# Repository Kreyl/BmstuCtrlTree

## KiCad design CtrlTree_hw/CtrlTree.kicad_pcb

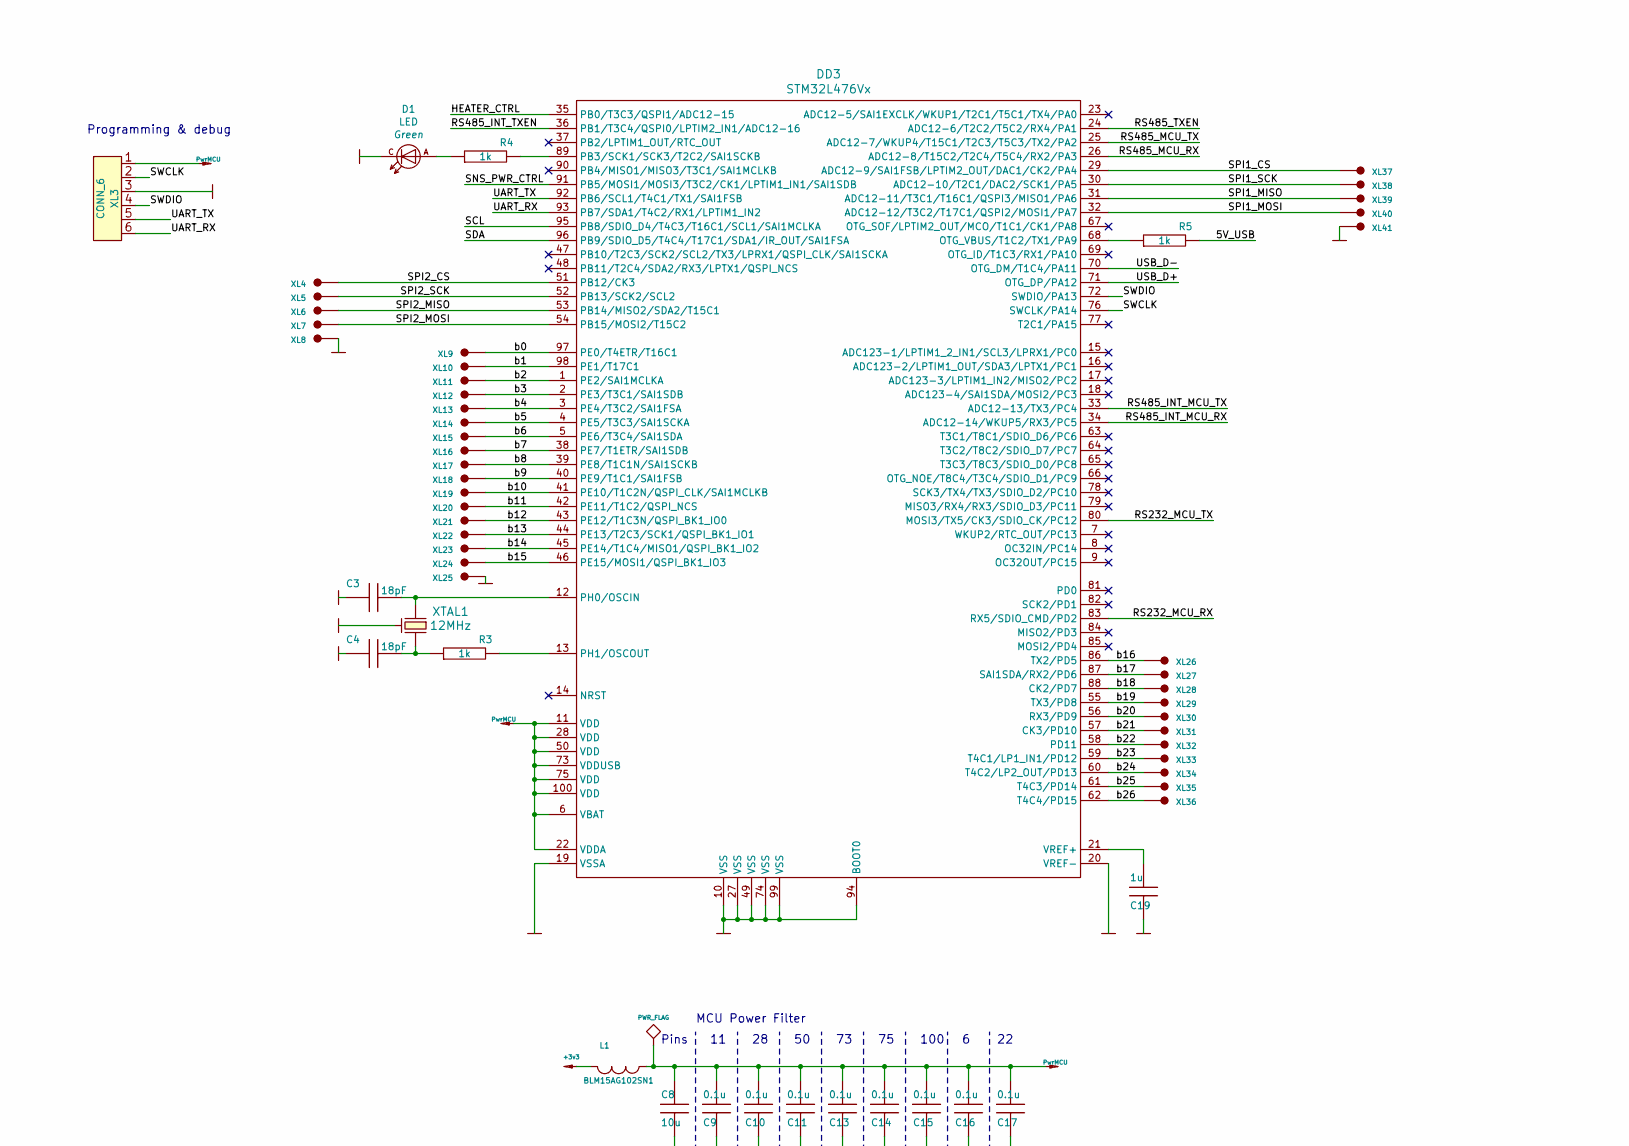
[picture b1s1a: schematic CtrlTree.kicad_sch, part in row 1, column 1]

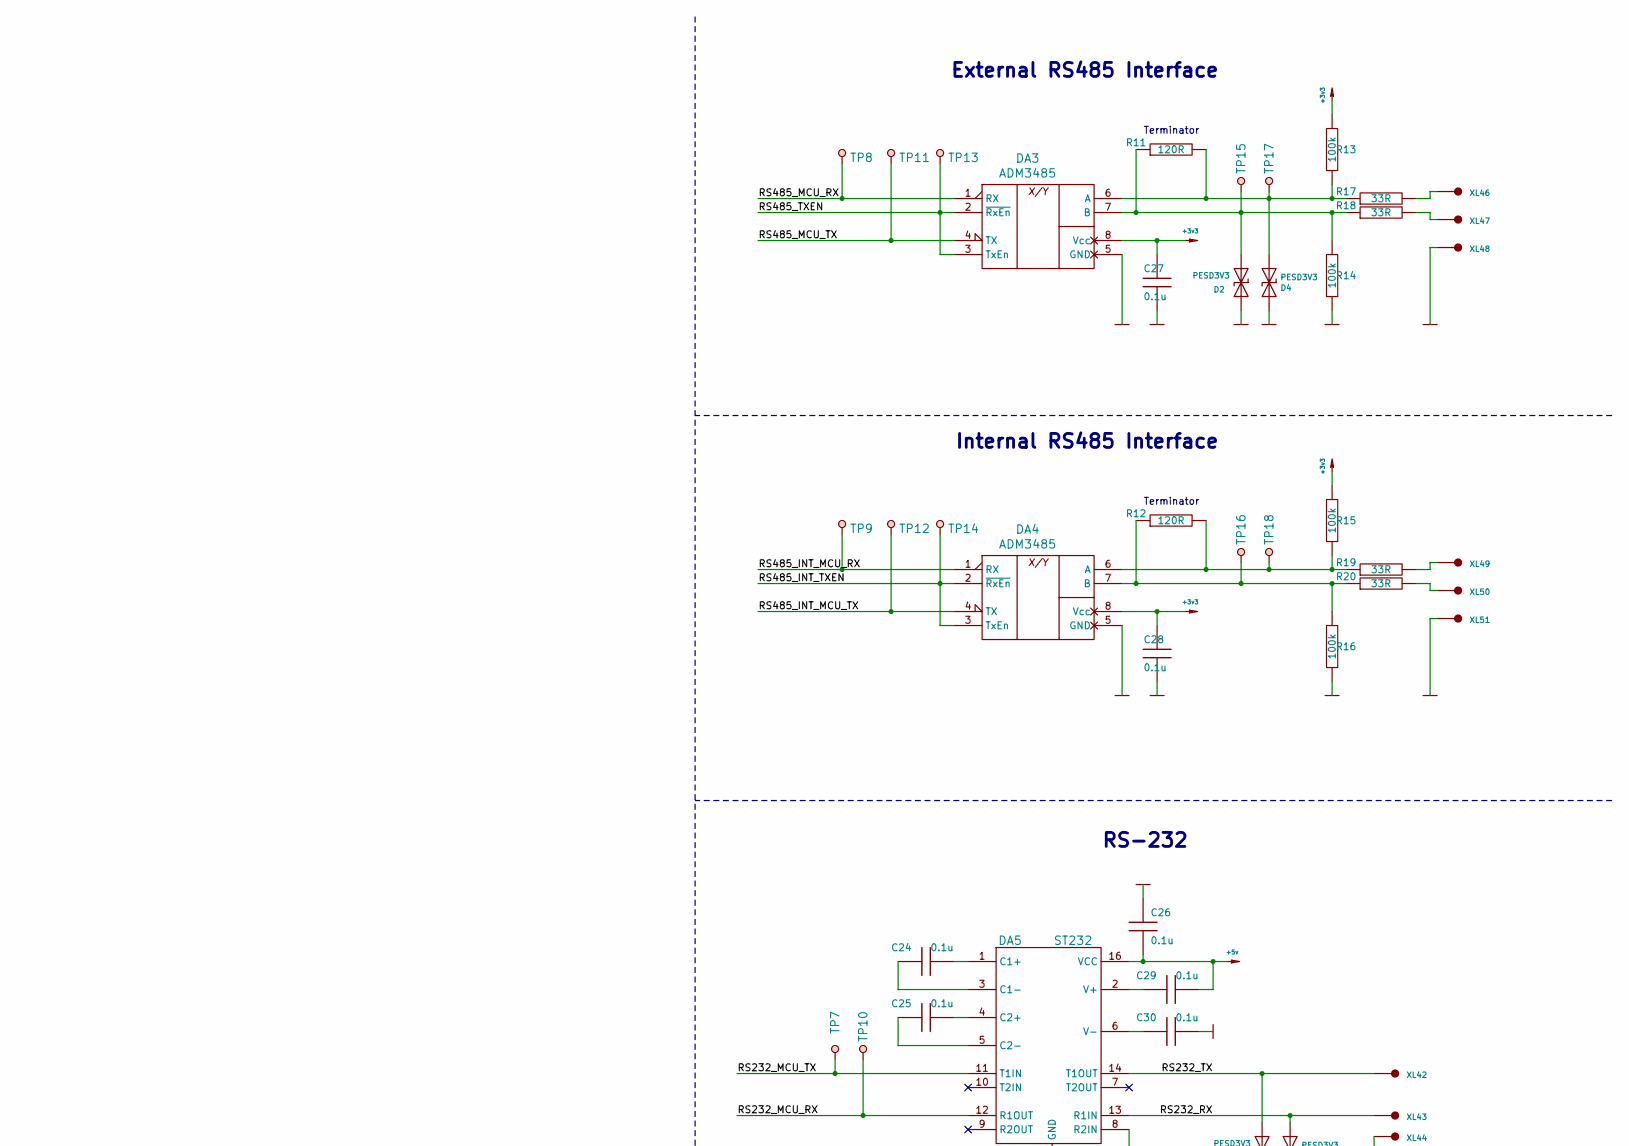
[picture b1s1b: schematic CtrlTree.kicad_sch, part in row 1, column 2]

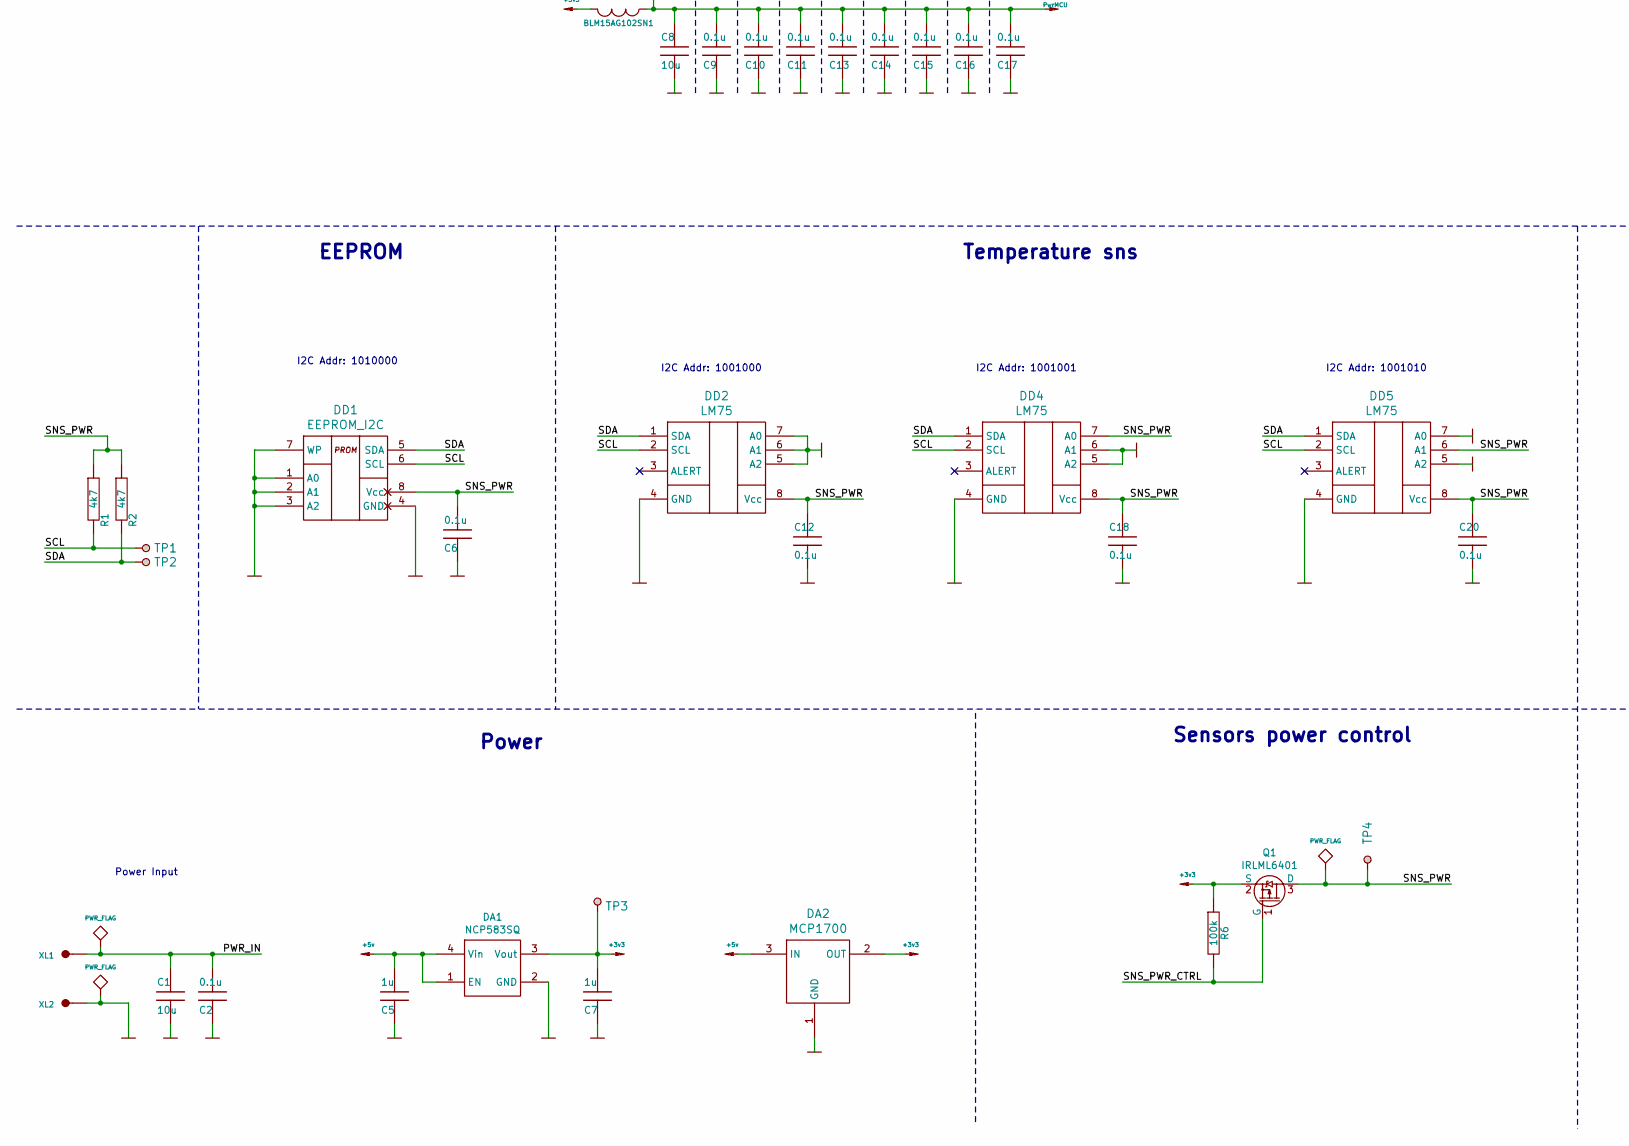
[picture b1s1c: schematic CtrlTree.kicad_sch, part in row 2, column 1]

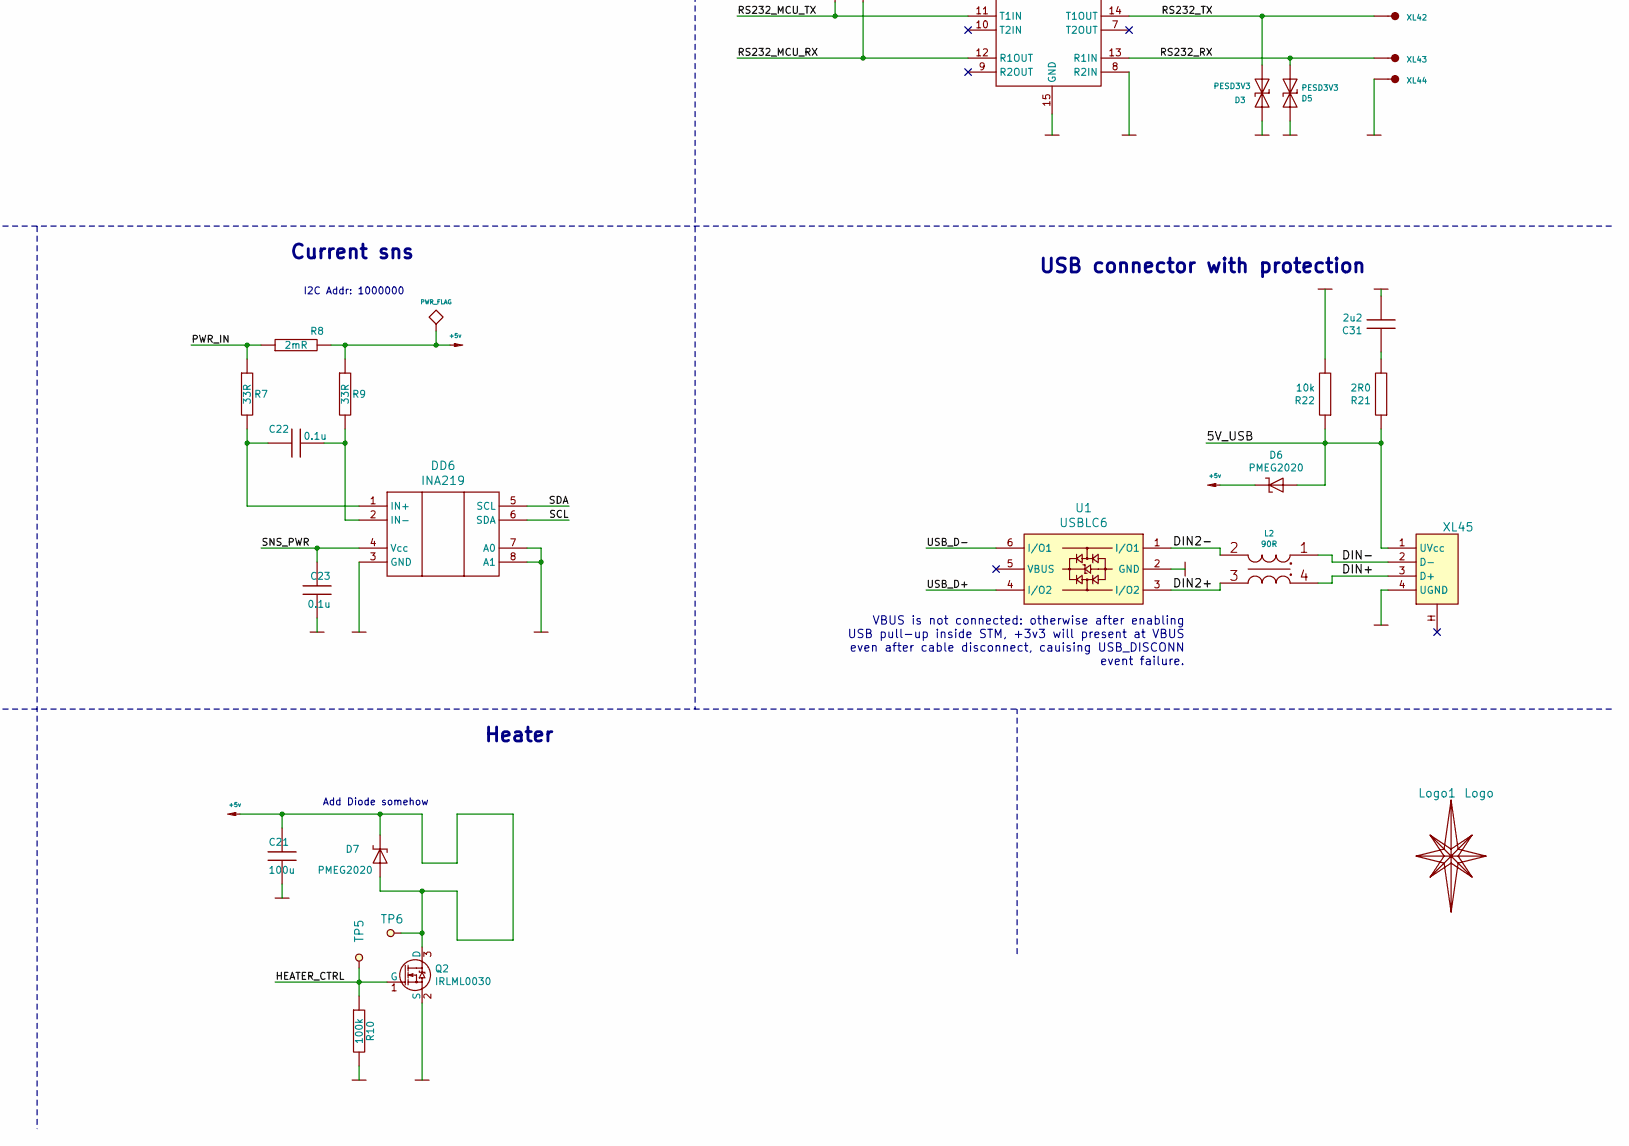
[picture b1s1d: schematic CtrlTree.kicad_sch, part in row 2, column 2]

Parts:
C1, C8: 10u; CAP_0603_Silks
C2, C6, C9, C10, C11, C12, C13, C14, C15, C16, C17, C18, C20, C22, C23, C24, C25, C26, C27, C28, C29, C30: 0.1u; CAP_0603_Silks
C3, C4: 18pF; CAP_0603_Silks
C5, C7, C19: 1u; CAP_0603_Silks
C21: 100u; CAP_1206
C31: 2u2; CAP_0603_Silks
D1: LED; LED_0603
D2, D3, D4, D5: PESD3V3; SOD323
D6, D7: PMEG2020; SOD323
DA1: NCP583SQ; SC82AB
DA2: MCP1700; SOT23-3A
DA3, DA4: ADM3485; SO8_150MIL
DA5: ST232; SO16_150MIL
DD1: EEPROM_I2C; SO8_150MIL
DD2, DD4, DD5: LM75; SO8_150MIL
DD3: STM32L476Vx; LQFP100
DD6: INA219; SOT23-8
L1: BLM15AG102SN1; IND_0402
L2: 90R; DLW21SN
Logo1: Logo; Ostranna_12d7_10d1
Q1: IRLML6401; SOT23-3
Q2: IRLML0030; SOT23-3
R1, R2: 4k7; RES_0603
R3, R4, R5: 1k; RES_0603
R6, R10, R13, R14, R15, R16: 100k; RES_0603
R7, R9, R17, R18, R19, R20: 33R; RES_0603
R8: 2mR; RES_2512
R11, R12: 120R; RES_0603
R21: 2R0; RES_0603
R22: 10k; RES_0603
TP1, TP2, TP3, TP4, TP5, TP6, TP7, TP8, TP9, TP10, TP11, TP12, TP13, TP14, TP15, TP16, TP17, TP18: TESTPOINT; TESTPOINT_1MM
U1: USBLC6; SOT23-6
XL1, XL2, XL4, XL5, XL6, XL7, XL8, XL9, XL10, XL11, XL12, XL13, XL14, XL15, XL16, XL17, XL18, XL19, XL20, XL21, XL22, XL23, XL24, XL25, XL26, XL27, XL28, XL29, XL30, XL31, XL32, XL33, XL34, XL35, XL36, XL37, XL38, XL39, XL40, XL41, XL42, XL43, XL44, XL46, XL47, XL48, XL49, XL50, XL51: CONN_GOST_1; Oval3x1.5
XL3: CONN_6; PLS-6_LOCK
XL45: USB_MICRO_2H; USB_B
XTAL1: 12MHz; 03225C4

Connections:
+3v3: C7.1, C27.2, C28.2, DA1.3 (Vout), DA2.2 (OUT), DA3.8 (Vcc), DA4.8 (Vcc), L1.2, Q1.2 (S), R6.1, R13.1, R15.1, TP3.1
+5v: C5.1, C21.2, C26.2, C29.2, D6.C, D7.A, D7.C, DA1.1 (EN), DA1.4 (Vin), DA2.3 (IN), DA5.16 (VCC), Q2.3 (D), R8.2, R9.1, TP6.1
/5V_USB: D6.A, R5.2, R21.1, R22.1, XL45.1 (UVcc)
/DIN2+: L2.3, U1.3 (I/O2)
/DIN2-: L2.2, U1.1 (I/O1)
/DIN+: L2.4, XL45.3 (D+)
/DIN-: L2.1, XL45.2 (D-)
/HEATER_CTRL: DD3.35 (PB0/T3C3/QSPI1/ADC12-15), Q2.1 (G), R10.1, TP5.1
/PWR_IN: C1.2, C2.1, R7.1, R8.1, XL1.1
/RS232_MCU_RX: DA5.12 (R1OUT), DD3.83 (RX5/SDIO_CMD/PD2), TP10.1
/RS232_MCU_TX: DA5.11 (T1IN), DD3.80 (MOSI3/TX5/CK3/SDIO_CK/PC12), TP7.1
/RS232_RX: D5.C, DA5.13 (R1IN), XL43.1
/RS232_TX: D3.C, DA5.14 (T1OUT), XL42.1
/RS485_INT_MCU_RX: DA4.1 (RX), DD3.34 (ADC12-14/WKUP5/RX3/PC5), TP9.1
/RS485_INT_MCU_TX: DA4.4 (TX), DD3.33 (ADC12-13/TX3/PC4), TP12.1
/RS485_INT_TXEN: DA4.2 (~RxEn), DA4.3 (TxEn), DD3.36 (PB1/T3C4/QSPI0/LPTIM2_IN1/ADC12-16), TP14.1
/RS485_MCU_RX: DA3.1 (RX), DD3.26 (ADC12-8/T15C2/T2C4/T5C4/RX2/PA3), TP8.1
/RS485_MCU_TX: DA3.4 (TX), DD3.25 (ADC12-7/WKUP4/T15C1/T2C3/T5C3/TX2/PA2), TP11.1
/RS485_TXEN: DA3.2 (~RxEn), DA3.3 (TxEn), DD3.24 (ADC12-6/T2C2/T5C2/RX4/PA1), TP13.1
/SCL: DD1.6 (SCL), DD2.2 (SCL), DD3.95 (PB8/SDIO_D4/T4C3/T16C1/SCL1/SAI1MCLKA), DD4.2 (SCL), DD5.2 (SCL), DD6.6 (SDA), R1.2, TP1.1
/SDA: DD1.5 (SDA), DD2.1 (SDA), DD3.96 (PB9/SDIO_D5/T4C4/T17C1/SDA1/IR_OUT/SAI1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), DD4.1 (SDA), DD5.1 (SDA), DD6.5 (SCL), R2.2, TP2.1
/SNS_PWR: C6.1, C12.2, C18.2, C20.2, C23.2, DD1.8 (Vcc), DD2.8 (Vcc), DD4.7 (A0), DD4.8 (Vcc), DD5.6 (A1), DD5.8 (Vcc), DD6.4 (Vcc), Q1.3 (D), R1.1, R2.1, TP4.1
/SNS_PWR_CTRL: DD3.91 (PB5/MOSI1/MOSI3/T3C2/CK1/LPTIM1_IN1/SAI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), Q1.1 (G), R6.2
/SPI1_CS: DD3.29 (ADC12-9/SAI1FSB/LPTIM2_OUT/DAC1/CK2/PA4), XL37.1
/SPI1_MISO: DD3.31 (ADC12-11/T3C1/T16C1/QSPI3/MISO1/PA6), XL39.1
/SPI1_MOSI: DD3.32 (ADC12-12/T3C2/T17C1/QSPI2/MOSI1/PA7), XL40.1
/SPI1_SCK: DD3.30 (ADC12-10/T2C1/DAC2/SCK1/PA5), XL38.1
/SPI2_CS: DD3.51 (PB12/CK3), XL4.1
/SPI2_MISO: DD3.53 (PB14/MISO2/SDA2/T15C1), XL6.1
/SPI2_MOSI: DD3.54 (PB15/MOSI2/T15C2), XL7.1
/SPI2_SCK: DD3.52 (PB13/SCK2/SCL2), XL5.1
/SWCLK: DD3.76 (SWCLK/PA14), XL3.2
/SWDIO: DD3.72 (SWDIO/PA13), XL3.4
/UART_RX: DD3.93 (PB7/SDA1/T4C2/RX1/LPTIM1_IN2), XL3.6
/UART_TX: DD3.92 (PB6/SCL1/T4C1/TX1/SAI1FSB), XL3.5
/USB_D+: DD3.71 (OTG_DP/PA12), U1.4 (I/O2)
/USB_D-: DD3.70 (OTG_DM/T1C4/PA11), U1.6 (I/O1)
/b0: DD3.97 (PE0/T4ETR/T16C1), XL9.1
/b1: DD3.98 (PE1/T17C1), XL10.1
/b2: DD3.1 (PE2/SAI1MCLKA), XL11.1
/b3: DD3.2 (PE3/T3C1/SAI1SDB), XL12.1
/b4: DD3.3 (PE4/T3C2/SAI1FSA), XL13.1
/b5: DD3.4 (PE5/T3C3/SAI1SCKA), XL14.1
/b6: DD3.5 (PE6/T3C4/SAI1SDA), XL15.1
/b7: DD3.38 (PE7/T1ETR/SAI1SDB), XL16.1
/b8: DD3.39 (PE8/T1C1N/SAI1SCKB), XL17.1
/b9: DD3.40 (PE9/T1C1/SAI1FSB), XL18.1
/b10: DD3.41 (PE10/T1C2N/QSPI_CLK/SAI1MCLKB), XL19.1
/b11: DD3.42 (PE11/T1C2/QSPI_NCS), XL20.1
/b12: DD3.43 (PE12/T1C3N/QSPI_BK1_IO0), XL21.1
/b13: DD3.44 (PE13/T2C3/SCK1/QSPI_BK1_IO1), XL22.1
/b14: DD3.45 (PE14/T1C4/MISO1/QSPI_BK1_IO2), XL23.1
/b15: DD3.46 (PE15/MOSI1/QSPI_BK1_IO3), XL24.1
/b16: DD3.86 (TX2/PD5), XL26.1
/b17: DD3.87 (SAI1SDA/RX2/PD6), XL27.1
/b18: DD3.88 (CK2/PD7), XL28.1
/b19: DD3.55 (TX3/PD8), XL29.1
/b20: DD3.56 (RX3/PD9), XL30.1
/b21: DD3.57 (CK3/PD10), XL31.1
/b22: DD3.58 (PD11), XL32.1
/b23: DD3.59 (T4C1/LP1_IN1/PD12), XL33.1
/b24: DD3.60 (T4C2/LP2_OUT/PD13), XL34.1
/b25: DD3.61 (T4C3/PD14), XL35.1
/b26: DD3.62 (T4C4/PD15), XL36.1
GND: C1.1, C2.2, C3.2, C4.2, C5.2, C6.2, C7.2, C8.1, C9.2, C10.2, C11.2, C12.1, C13.2, C14.2, C15.2, C16.2, C17.2, C18.1, C19.2, C20.1, C21.1, C23.1, C26.1, C27.1, C28.1, C30.2, C31.2, D1.C, D2.A, D3.A, D4.A, D5.A, DA1.2 (GND), DA2.1 (GND), DA3.5 (GND), DA4.5 (GND), DA5.8 (R2IN), DA5.15 (GND), DD1.1 (A0), DD1.2 (A1), DD1.3 (A2), DD1.4 (GND), DD1.7 (WP), DD2.4 (GND), DD2.5 (A2), DD2.6 (A1), DD2.7 (A0), DD3.10 (VSS), DD3.19 (VSSA), DD3.20 (VREF-), DD3.27 (VSS), DD3.49 (VSS), DD3.74 (VSS), DD3.94 (BOOT0), DD3.99 (VSS), DD4.4 (GND), DD4.5 (A2), DD4.6 (A1), DD5.4 (GND), DD5.5 (A2), DD5.7 (A0), DD6.3 (GND), DD6.7 (A0), DD6.8 (A1), Q2.2 (S), R10.2, R14.2, R16.2, R22.2, U1.2 (GND), XL2.1, XL3.3, XL8.1, XL25.1, XL41.1, XL44.1, XL45.4 (UGND), XL48.1, XL51.1, XTAL1.H
unnamed: C3.1, DD3.12 (PH0/OSCIN), XTAL1.1
unnamed: C4.1, R3.1, XTAL1.2
unnamed: C19.1, DD3.21 (VREF+)
unnamed: C22.1, DD6.2 (IN-), R9.2
unnamed: C22.2, DD6.1 (IN+), R7.2
unnamed: C24.1, DA5.3 (C1-)
unnamed: C24.2, DA5.1 (C1+)
unnamed: C25.1, DA5.5 (C2-)
unnamed: C25.2, DA5.4 (C2+)
unnamed: C29.1, DA5.2 (V+)
unnamed: C30.1, DA5.6 (V-)
unnamed: C31.1, R21.2
unnamed: D1.A, R4.1
unnamed: D2.C, DA3.7 (B), R11.1, R14.1, R18.1, TP15.1
unnamed: D4.C, DA3.6 (A), R11.2, R13.2, R17.1, TP17.1
unnamed: DA4.6 (A), R12.2, R15.2, R19.1, TP18.1
unnamed: DA4.7 (B), R12.1, R16.1, R20.1, TP16.1
unnamed: DD3.13 (PH1/OSCOUT), R3.2
unnamed: DD3.68 (OTG_VBUS/T1C2/TX1/PA9), R5.1
unnamed: DD3.89 (PB3/SCK1/SCK3/T2C2/SAI1SCKB), R4.2
unnamed: R17.2, XL46.1
unnamed: R18.2, XL47.1
unnamed: R19.2, XL49.1
unnamed: R20.2, XL50.1
PwrMCU: C8.2, C9.1, C10.1, C11.1, C13.1, C14.1, C15.1, C16.1, C17.1, DD3.6 (VBAT), DD3.11 (VDD), DD3.22 (VDDA), DD3.28 (VDD), DD3.50 (VDD), DD3.73 (VDDUSB), DD3.75 (VDD), DD3.100 (VDD), L1.1, XL3.1

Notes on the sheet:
Programming & debug
Power Input
I2C Addr: 1010000
EEPROM
Power
Pins
I2C Addr: 1001000
MCU Power Filter
100
Temperature sns
I2C Addr: 1001001
Sensors power control
I2C Addr: 1001010
Current sns
I2C Addr: 1000000
Add Diode somehow
Heater
RS-232
Terminator
VBUS is not connected: otherwise after enabling USB pull-up inside STM, +3v3 will present at VBUS even after cable disconnect, cauising USB_DISCONN event failure.
External RS485 Interface
Internal RS485 Interface
USB connector with protection

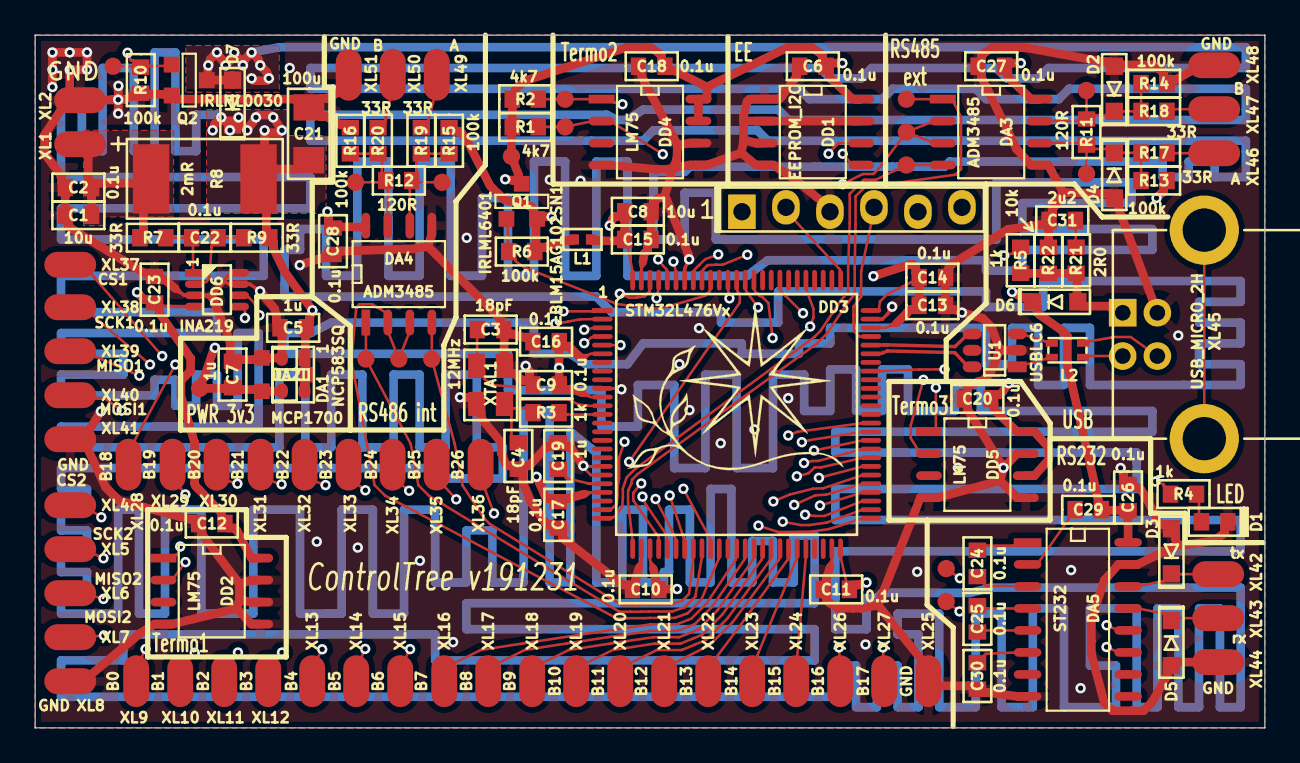
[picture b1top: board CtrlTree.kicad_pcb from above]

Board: 4 copper layers, 71.0 x 40.0 mm, 147 parts (0 on the bottom side), 90 nets.

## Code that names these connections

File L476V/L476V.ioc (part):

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Mcu.Name=STM32L476V(C-E-G)Tx
Mcu.Package=LQFP100
Mcu.UserName=STM32L476VGTx
PA1.Mode=Hardware Flow Control (RS485)
PA1.Signal=USART2_DE
PA11.Mode=Device_Only
PA11.Signal=USB_OTG_FS_DM
PA12.Mode=Device_Only
PA12.Signal=USB_OTG_FS_DP
PA13\ (JTMS-SWDIO).Mode=Serial_Wire
PA13\ (JTMS-SWDIO).Signal=SYS_JTMS-SWDIO
PA14\ (JTCK-SWCLK).Mode=Serial_Wire
PA14\ (JTCK-SWCLK).Signal=SYS_JTCK-SWCLK
PA2.Mode=Asynchronous
PA2.Signal=USART2_TX
PA3.Mode=Asynchronous
PA3.Signal=USART2_RX
PA4.Mode=NSS_Signal_Hard_Output
PA4.Signal=SPI1_NSS
PA5.Mode=Full_Duplex_Master
PA5.Signal=SPI1_SCK
PA6.Mode=Full_Duplex_Master
PA6.Signal=SPI1_MISO
PA7.Mode=Full_Duplex_Master
PA7.Signal=SPI1_MOSI
PA9.Mode=Activate_VBUS
PA9.Signal=USB_OTG_FS_VBUS
PB0.Signal=S_TIM3_CH3
PB1.Mode=Hardware Flow Control (RS485)
PB1.Signal=USART3_DE
PB12.Mode=NSS_Signal_Hard_Output
PB12.Signal=SPI2_NSS
PB13.Mode=Full_Duplex_Master
PB13.Signal=SPI2_SCK
PB14.Mode=Full_Duplex_Master
PB14.Signal=SPI2_MISO
PB15.Mode=Full_Duplex_Master
PB15.Signal=SPI2_MOSI
PB4\ (NJTRST).Mode=CTS_RTS
PB4\ (NJTRST).Signal=UART5_RTS
PB5.Mode=CTS_RTS
PB5.Signal=UART5_CTS
PB6.Mode=Asynchronous
PB6.Signal=USART1_TX
PB7.Mode=Asynchronous
PB7.Signal=USART1_RX
PB8.Mode=I2C
PB8.Signal=I2C1_SCL
PB9.Mode=I2C
PB9.Signal=I2C1_SDA
PC12.Mode=Asynchronous
PC12.Signal=UART5_TX
PC4.Mode=Asynchronous
PC4.Signal=USART3_TX
PC5.Mode=Asynchronous
PC5.Signal=USART3_RX
PD10.Signal=GPIO_Output
PD11.Signal=GPIO_Output
PD12.Signal=GPIO_Output
PD13.Signal=GPIO_Output
PD14.Signal=GPIO_Output
PD15.Signal=GPIO_Output
PD2.Mode=Asynchronous
PD2.Signal=UART5_RX
PD5.Signal=GPIO_Output
PD6.Signal=GPIO_Output
PD7.Signal=GPIO_Output
PD8.Signal=GPIO_Output
PD9.Signal=GPIO_Output
PE0.Signal=GPIO_Output
PE1.Signal=GPIO_Output
PE10.Signal=GPIO_Output
PE11.Signal=GPIO_Output
PE12.Signal=GPIO_Output
PE13.Signal=GPIO_Output
PE14.Signal=GPIO_Output
PE15.Signal=GPIO_Output
PE2.Signal=GPIO_Output
PE3.Signal=GPIO_Output
PE4.Signal=GPIO_Output
PE5.Signal=GPIO_Output
PE6.Signal=GPIO_Output
PE7.Signal=GPIO_Output
PE8.Signal=GPIO_Output
PE9.Signal=GPIO_Output
PH0-OSC_IN\ (PH0).Mode=HSE-External-Oscillator
PH0-OSC_IN\ (PH0).Signal=RCC_OSC_IN
PH1-OSC_OUT\ (PH1).Mode=HSE-External-Oscillator
PH1-OSC_OUT\ (PH1).Signal=RCC_OSC_OUT
RCC.HSE_VALUE=12000000
RCC.SYSCLKFreq_VALUE=48000000
RCC.SYSCLKSource=RCC_SYSCLKSOURCE_PLLCLK
board=custom

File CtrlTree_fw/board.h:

/*
 * board.h
 *
 *  Created on: 05 08 2018
 *      Author: Kreyl
 */

#pragma once

// ==== General ====
#define APP_NAME            "BMSTU CtrlTree"

// MCU type as defined in the ST header.
#define STM32L476xx

// Freq of external crystal if any. Leave it here even if not used.
#define CRYSTAL_FREQ_HZ         12000000

// OS timer settings
#define STM32_ST_IRQ_PRIORITY   2
#define STM32_ST_USE_TIMER      5
#define SYS_TIM_CLK             (Clk.APB1FreqHz)    // Timer 5 is clocked by APB1

//  Periphery
#define I2C1_ENABLED            TRUE
#define I2C2_ENABLED            FALSE
#define I2C3_ENABLED            FALSE
#define SIMPLESENSORS_ENABLED   TRUE
#define BUTTONS_ENABLED         FALSE

#define ADC_REQUIRED            FALSE
#define STM32_DMA_REQUIRED      TRUE    // Leave this macro name for OS

#define FILEBUF_SZ              65535

#if 1 // ========================== GPIO =======================================
// EXTI
#define INDIVIDUAL_EXTI_IRQ_REQUIRED    FALSE

// DBG UART
#define UART_GPIO       GPIOB
#define UART_TX_PIN     6
#define UART_RX_PIN     7
// Ext RS485
#define RS485_EXT_TXEN  GPIOA, 1, AF7
#define RS485_EXT_TX    GPIOA, 2
#define RS485_EXT_RX    GPIOA, 3
// Ext RS232
#define RS232_TX        GPIOC, 12
#define RS232_RX        GPIOD, 2
// Int RS485
#define RS485_INT_TXEN  GPIOB, 1, AF7
#define RS485_INT_TX    GPIOC, 4
#define RS485_INT_RX    GPIOC, 5

// DBG LED
#define LED_PIN         GPIOB, 3, omPushPull

// TControl
#define HEATER_TOP      1000
#define HEATER_MAX_V    702.0 // To allow 2A max
#define HEATER_CTRL     GPIOB, 0, TIM3, 3, invNotInverted, omPushPull, (HEATER_TOP-1)

// I2C
#define I2C1_GPIO       GPIOB
#define I2C1_SCL        8
#define I2C1_SDA        9

#define SNS_PWR_CTRL    GPIOB, 5

// I2C Alternate Function
#define I2C_AF          AF4

// USB
#define USB_DM          GPIOA, 11
#define USB_DP          GPIOA, 12
#define USB_AF          AF10
// USB detect
#define USB_DETECT_PIN  GPIOA, 9

#endif // GPIO

#if 1 // =========================== I2C =======================================
// i2cclkPCLK1, i2cclkSYSCLK, i2cclkHSI
#define I2C_CLK_SRC     i2cclkHSI
#define I2C_BAUDRATE_HZ 400000
#endif

#if ADC_REQUIRED // ======================= Inner ADC ==========================
// Clock divider: clock is generated from the APB2
#define ADC_CLK_DIVIDER		adcDiv2

// ADC channels
#define ADC_BATTERY_CHNL 	14
// ADC_VREFINT_CHNL
#define ADC_CHANNELS        { ADC_BATTERY_CHNL, ADC_VREFINT_CHNL }
#define ADC_CHANNEL_CNT     2   // Do not use countof(AdcChannels) as preprocessor does not know what is countof => cannot check
#define ADC_SAMPLE_TIME     ast24d5Cycles
#define ADC_OVERSAMPLING_RATIO  64   // 1 (no oversampling), 2, 4, 8, 16, 32, 64, 128, 256
#endif

#if 1 // =========================== DMA =======================================
// ==== Uart ====
// Remap is made automatically if required
#define UART_DMA_TX     STM32_DMA_STREAM_ID(1, 4)
#define UART_DMA_RX     STM32_DMA_STREAM_ID(1, 5)
#define UART_DMA_CHNL   2
#define UART_DMA_TX_MODE(Chnl) (STM32_DMA_CR_CHSEL(Chnl) | DMA_PRIORITY_LOW | STM32_DMA_CR_MSIZE_BYTE | STM32_DMA_CR_PSIZE_BYTE | STM32_DMA_CR_MINC | STM32_DMA_CR_DIR_M2P | STM32_DMA_CR_TCIE)
#define UART_DMA_RX_MODE(Chnl) (STM32_DMA_CR_CHSEL(Chnl) | DMA_PRIORITY_MEDIUM | STM32_DMA_CR_MSIZE_BYTE | STM32_DMA_CR_PSIZE_BYTE | STM32_DMA_CR_MINC | STM32_DMA_CR_DIR_P2M | STM32_DMA_CR_CIRC)

#define RS485EXT_DMA_TX STM32_DMA_STREAM_ID(1, 7)
#define RS485EXT_DMA_RX STM32_DMA_STREAM_ID(1, 6)

#define RS485INT_DMA_TX STM32_DMA_STREAM_ID(1, 2)
#define RS485INT_DMA_RX STM32_DMA_STREAM_ID(1, 3)

#define RS232_DMA_TX    STM32_DMA_STREAM_ID(2, 1)
#define RS232_DMA_RX    STM32_DMA_STREAM_ID(2, 2)

// ==== I2C ====
#define I2C1_DMA_TX     STM32_DMA_STREAM_ID(2, 7)
#define I2C1_DMA_RX     STM32_DMA_STREAM_ID(2, 6)
#define I2C1_DMA_CHNL   5
#define I2C2_DMA_TX     STM32_DMA_STREAM_ID(1, 4)
#define I2C2_DMA_RX     STM32_DMA_STREAM_ID(1, 5)
#define I2C2_DMA_CHNL   3
#define I2C3_DMA_TX     STM32_DMA_STREAM_ID(1, 2)
#define I2C3_DMA_RX     STM32_DMA_STREAM_ID(1, 3)
#define I2C3_DMA_CHNL   3

#if ADC_REQUIRED
#define ADC_DMA         STM32_DMA1_STREAM1
#define ADC_DMA_MODE    STM32_DMA_CR_CHSEL(0) |   /* DMA1 Stream1 Channel0 */ \
                        DMA_PRIORITY_LOW | \
                        STM32_DMA_CR_MSIZE_HWORD | \
                        STM32_DMA_CR_PSIZE_HWORD | \
                        STM32_DMA_CR_MINC |       /* Memory pointer increase */ \
                        STM32_DMA_CR_DIR_P2M |    /* Direction is peripheral to memory */ \
                        STM32_DMA_CR_TCIE         /* Enable Transmission Complete IRQ */
#endif // ADC

#endif // DMA

#if 1 // ========================== USART ======================================
#define PRINTF_FLOAT_EN TRUE
#define UART_TXBUF_SZ   4096
#define UART_RXBUF_SZ   1024
#define CMD_BUF_SZ      1024

#define CMD_UART        USART1

#define CMD_UART_PARAMS \
    USART1, UART_GPIO, UART_TX_PIN, UART_GPIO, UART_RX_PIN, \
    UART_DMA_TX, UART_DMA_RX, UART_DMA_TX_MODE(UART_DMA_CHNL), UART_DMA_RX_MODE(UART_DMA_CHNL), \
    uartclkHSI // Use independent clock

#define RS485EXT_PARAMS \
    USART2, RS485_EXT_TX, RS485_EXT_RX, \
    RS485EXT_DMA_TX, RS485EXT_DMA_RX, UART_DMA_TX_MODE(UART_DMA_CHNL), UART_DMA_RX_MODE(UART_DMA_CHNL), \
    uartclkHSI // Use independent clock

#define RS485INT_PARAMS \
    USART3, RS485_INT_TX, RS485_INT_RX, \
    RS485INT_DMA_TX, RS485INT_DMA_RX, UART_DMA_TX_MODE(UART_DMA_CHNL), UART_DMA_RX_MODE(UART_DMA_CHNL), \
    uartclkHSI // Use independent clock

#define RS232_PARAMS \
    UART5, RS232_TX, RS232_RX, \
    RS232_DMA_TX, RS232_DMA_RX, UART_DMA_TX_MODE(UART_DMA_CHNL), UART_DMA_RX_MODE(UART_DMA_CHNL), \
    uartclkHSI // Use independent clock

#endif

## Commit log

2019-11-16 sch done
2019-12-30 Layout started
2019-12-31 + Gerbers ready
2020-03-22 + USB works
2020-05-02 * Switch to atollic + table management commands Not saved to EE, though
2020-05-02 + Save/Load table from EE
2020-05-03 Proceeding with commands for slave
2020-05-03 + Settings save/load + GpioReg
2020-05-03 + GetGpio on AllStates
2020-05-03 Common comands are sent to master using 0 address
2020-05-03 + _sbrk * Buffers moved to SRAM1, BSS -- to SRAM2 + WRSPI
2020-05-03 + Receive file by UART + Transmit it by SPI
2020-05-03 Read binary buf seems ok
2020-05-04 + Usb Receive / transmit File
2020-05-04 + HostRS485 works + Scan + GetDevList +GetAllStates
2020-05-04 + Clock setup if no quartz + Cmd forward
2020-05-04 + AddDevice and PutDevice change real device params
2020-05-05 + Transmitting files ok
2020-05-05 + Firmware version in state + CRC16 algorythm
2020-05-06 + CRC calculator + fw update started
2020-05-06 Completing fw update
2020-05-06 + FW update works on master
2020-05-06 + Slave Fw update
2020-05-16 + Cmd.Get
2020-05-17 + TControl
2020-06-06 + Write regs and Save regs for HMC821 and ADF5356
2020-06-08 + Regs set and save + ADF5356 freq set and save
2020-06-13 * ADF5356: SetRegs take values of uint32 only
2020-06-13 * TControl measures 3 sns
2020-06-23 + CS control Params of transmission Settings
2020-07-13 + saveregs * RReply
2020-07-28 * Fixed Avg t bug
2020-08-28 + Reload regs
